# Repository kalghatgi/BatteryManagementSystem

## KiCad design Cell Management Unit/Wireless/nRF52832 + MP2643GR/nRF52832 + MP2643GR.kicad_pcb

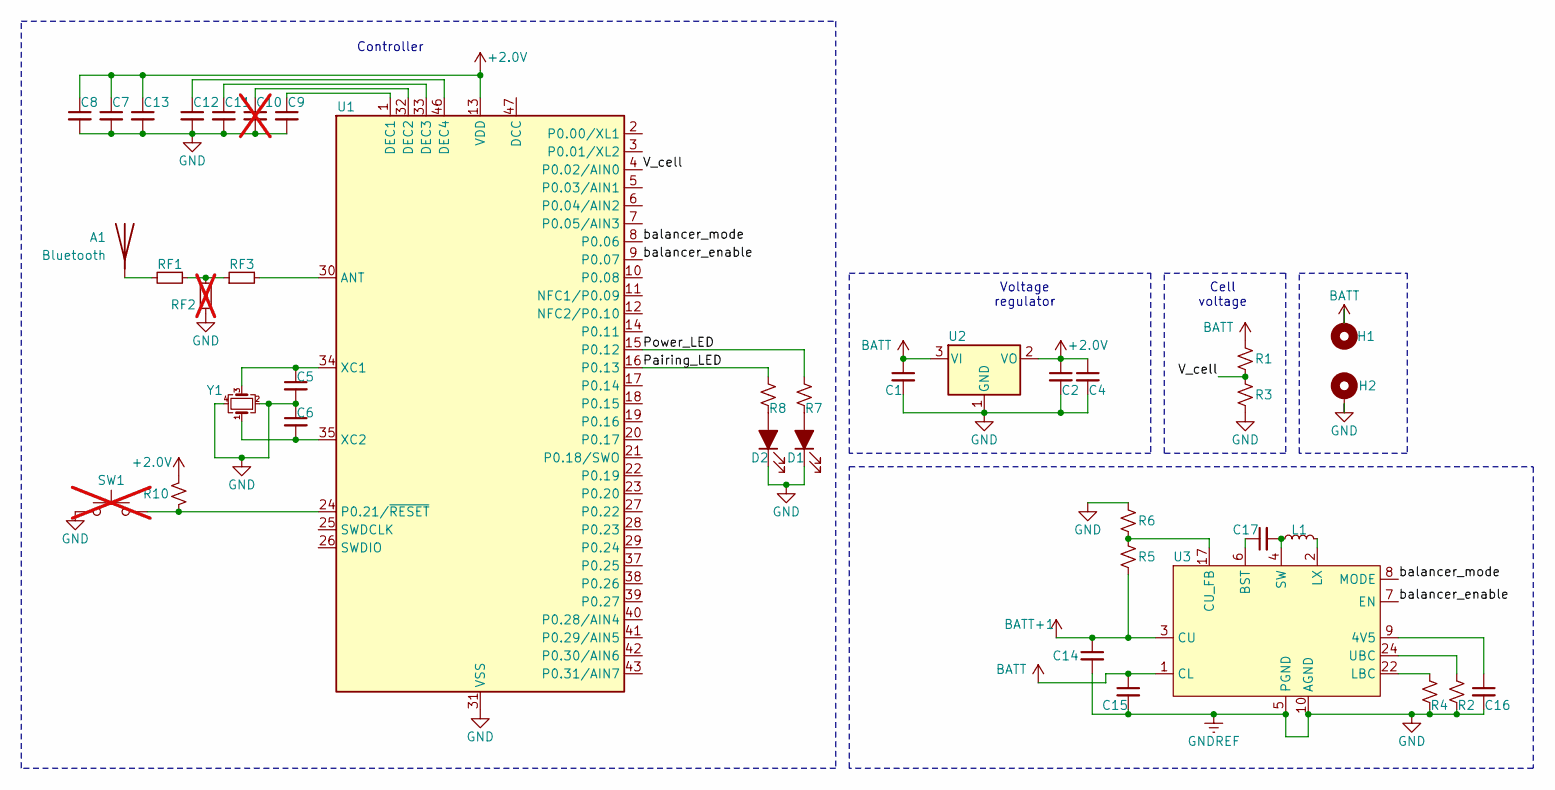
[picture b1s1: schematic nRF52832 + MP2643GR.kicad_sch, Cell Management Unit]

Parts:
A1: Bluetooth; L_1206_3216Metric; MPN RFANT3216120A5T
C1: 1uF, 10V; C_0402_1005Metric
C2, C4: 10uF, 4V; C_0402_1005Metric
C5, C6: 10pF, 4V; C_0402_1005Metric
C7, C9, C13: 100nF, 4V; C_0402_1005Metric
C8: 4.7uF, 4V; C_0402_1005Metric
C10: 100nF, 4V; C_0201_0603Metric; not fitted
C11: 100pF, 4V; C_0201_0603Metric
C12: 1uF, 4V; C_0402_1005Metric
C14: 22uF, >=10V, 0805; C_0805_2012Metric
C15: 22uF, >=6.3V, 0603; C_0603_1608Metric
C16: 1uF, >=10V, 0402; C_0402_1005Metric
C17: 22uF, >=10V, 0402; C_0402_1005Metric
D1: Red; LED_0402_1005Metric; MPN BL-HJE37A-AV-TRB
D2: Blue; LED_0402_1005Metric; MPN IN-S42BT5B
H1, H2: MountingHole_Pad; MountingHole_5.3mm_M5_Pad_Via
L1: 2.2uH, <50mOhm; L_Coilcraft_XxL4030; MPN ASPI-4030S-2R2N-T
R1: 15K, 62.5mW, <=1%, 0402; R_0402_1005Metric
R2: 107K, 62.5mW, 0402; R_0402_1005Metric
R3: 10K, 62.5mW, <= 1%, 0402; R_0402_1005Metric
R4: 133K, 62.5mW, <= 1%, 0402; R_0402_1005Metric
R5, R6: 10K, 62.5mW, <= 1%; R_0402_1005Metric
R7, R8: 4.7K, 62.5mW, 0402; R_0402_1005Metric
R10: 2.2K, 62.5mW; R_0402_1005Metric
RF1, RF3: C_0201_0603Metric
RF2: 0R, 62.5mW; C_0201_0603Metric; not fitted
SW1: SPST; SW_SPST_B3U-1000P; not fitted
U1: nRF52832-QFxx; QFN-48-1EP_6x6mm_P0.4mm_EP4.6x4.6mm
U2: 2.0V, >100mA; SOT-23; MPN MCP1700T-2002E-TT
U3: MP2643GR-Z; MP2643
Y1: 32MHz, 10ppm; US3200005Z_1612

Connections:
+2.0V: C2.1, C4.1, C7.1, C8.1, C13.1, R10.1, U1.13 (VDD), U1.36 (VDD), U1.48 (VDD), U2.2 (VO)
/Pairing_LED: R8.1, U1.16 (P0.13)
/Power_LED: R7.1, U1.15 (P0.12)
/V_cell: R1.2, R3.1, U1.4 (P0.02/AIN0)
/balancer_enable: U1.9 (P0.07), U3.7 (EN)
/balancer_mode: U1.8 (P0.06), U3.8 (MODE)
BATT: C1.1, C15.1, H1.1, R1.1, U2.3 (VI), U3.1 (CL)
BATT+1: C14.1, R5.2, U3.3 (CU)
GND: C1.2, C2.2, C4.2, C5.2, C6.1, C7.2, C8.2, C9.2, C10.2, C11.2, C12.2, C13.2, C14.2, C15.2, C16.2, D1.1 (K), D2.1 (K), H2.1, R2.2, R3.2, R4.2, R6.1, RF2.1, SW1.1, U1.31 (VSS), U1.45 (VSS), U1.49 (VSS), U2.1 (GND), U3.5 (PGND), U3.10 (AGND), U3.11 (AGND), U3.12 (AGND), U3.13 (AGND), U3.14 (AGND), U3.15 (AGND), U3.16 (AGND), U3.23 (AGND), U3.25 (AGND), U3.26 (AGND), Y1.2, Y1.4
LOGIC: C16.1, U3.9 (4V5), U3.18 (LOGIC)
unnamed: A1.1 (A), RF1.2
unnamed: D1.2 (A), R7.2
unnamed: D2.2 (A), R8.2
unnamed: RF1.1, RF2.2, RF3.1
unnamed: RF3.2, U1.30 (ANT)
unnamed: C9.1, U1.1 (DEC1)
unnamed: C10.1, U1.32 (DEC2)
unnamed: C11.1, U1.33 (DEC3)
unnamed: C12.1, U1.46 (DEC4)
unnamed: R10.2, SW1.2, U1.24 (P0.21/~RESET)
unnamed: C5.1, U1.34 (XC1), Y1.3
unnamed: C6.2, U1.35 (XC2), Y1.1
unnamed: C17.1, U3.6 (BST)
unnamed: R5.1, R6.2, U3.17 (CU_FB)
unnamed: R4.1, U3.22 (LBC)
unnamed: L1.2, U3.2 (LX)
unnamed: C17.2, L1.1, U3.4 (SW)
unnamed: R2.1, U3.24 (UBC)

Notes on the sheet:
Controller
Cell voltage
Voltage regulator

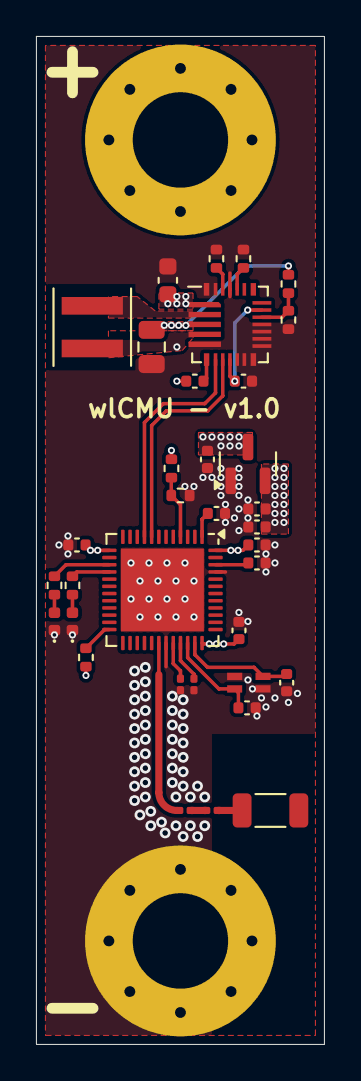
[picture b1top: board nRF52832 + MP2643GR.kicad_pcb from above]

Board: 4 copper layers, 16.0 x 56.0 mm, 37 parts (0 on the bottom side), 28 nets.

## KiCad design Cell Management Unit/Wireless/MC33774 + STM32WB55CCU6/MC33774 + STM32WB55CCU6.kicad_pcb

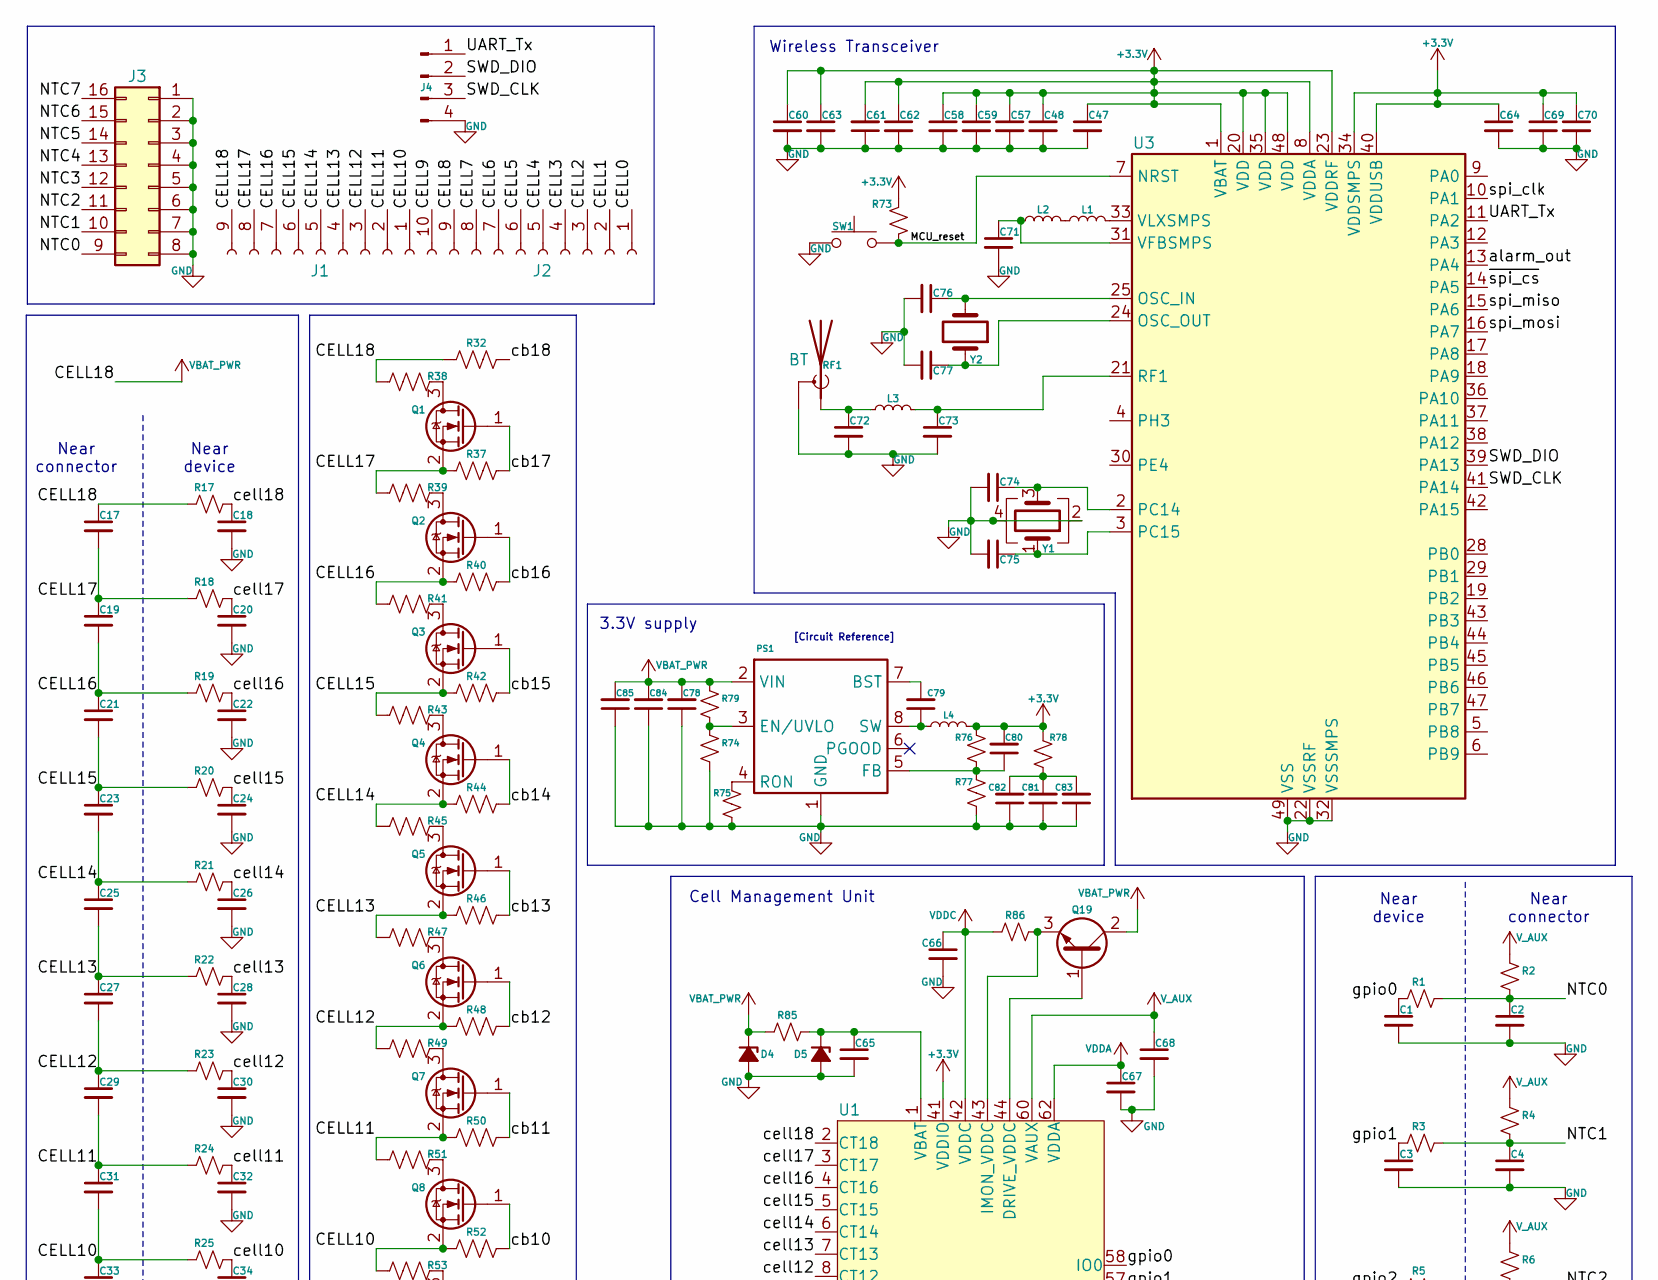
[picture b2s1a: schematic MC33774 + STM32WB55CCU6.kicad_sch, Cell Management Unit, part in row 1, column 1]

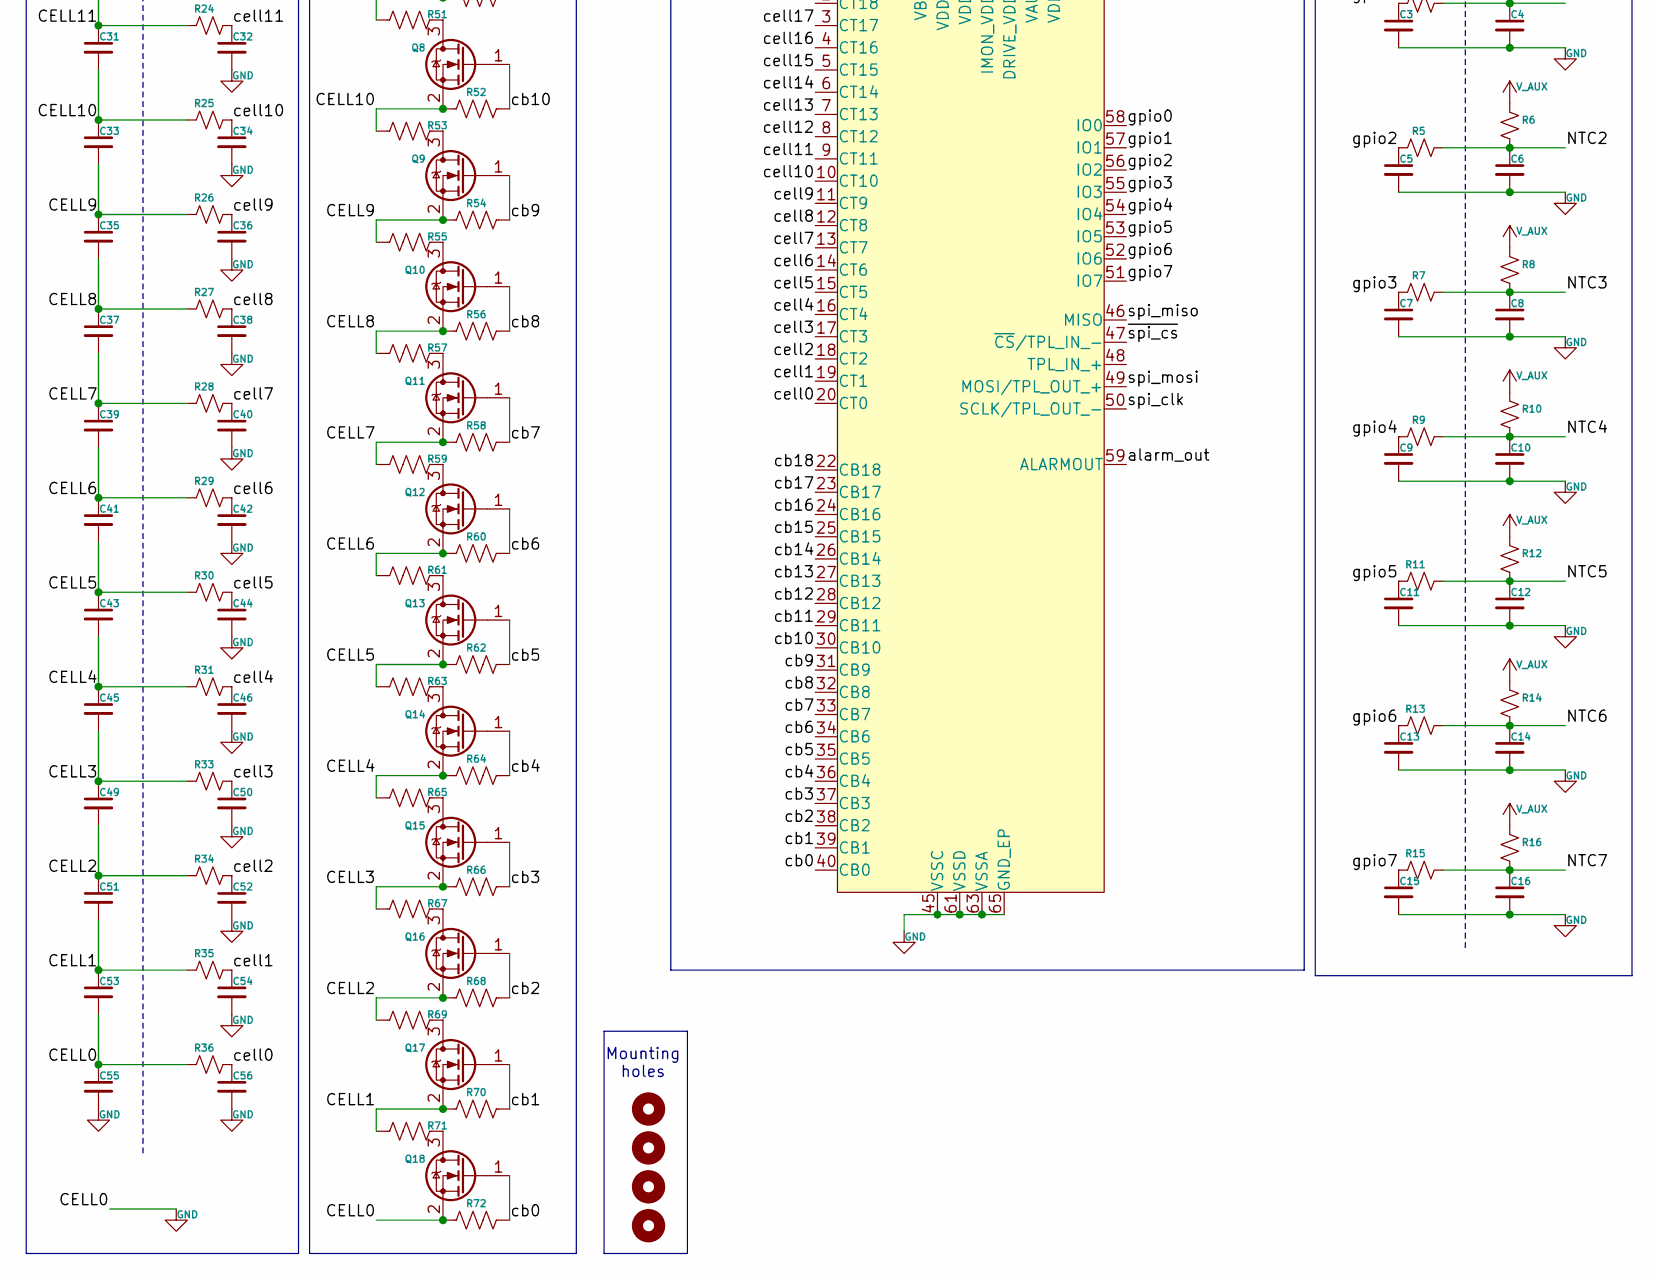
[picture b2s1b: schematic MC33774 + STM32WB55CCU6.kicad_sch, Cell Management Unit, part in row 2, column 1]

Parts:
C1, C2, C3, C4, C5, C6, C7, C8, C9, C10, C11, C12, C13, C14, C15, C16, C17, C19, C21, C23, C25, C27, C29, C31, C33, C35, C37, C39, C41, C43, C45, C49, C51, C53, C55: 47nF 10V 0402; C_0402_1005Metric
C18, C20, C22, C24, C26, C28, C30, C32, C34, C36, C38, C40, C42, C44, C46, C50, C52, C54, C56: 47nF 100V 0603; C_0603_1608Metric
C47, C48, C57, C59, C60, C62, C64, C70: 100nF 6.3V 0402; C_0402_1005Metric; MPN cc0402zpy5v7bb104
C58, C69, C71: 4.7uF 6.3V 0402; C_0402_1005Metric; MPN cl05a475mq5nrnc
C61: 1uF 6.3V 0402; C_0402_1005Metric; MPN cl05a105kq5nnnc
C63: 100pF 6.3V 0402; C_0402_1005Metric
C65: 100nF 100V 0805; C_0805_2012Metric
C66: 470nF 25V 0402; C_0402_1005Metric
C67, C68: 100nF 25V 0402; C_0402_1005Metric
C72: 1pF 6.3V 0402; C_0402_1005Metric
C73: 1.5pF 6.3V 0402; C_0402_1005Metric
C74, C75: 18pF 6.3V 0603; C_0603_1608Metric; MPN c0805c180m3hactu
C76, C77: 9pF 6.3V 0603; C_0603_1608Metric; MPN mc0603n9r0d500ct
C78, C84, C85: 1uF 100V 1206; C_1210_3225Metric
C79: 2.2nF 25V 0402; C_0402_1005Metric
C80: 100pF 25V 0805; C_0603_1608Metric
C81, C82, C83: 2.2uF 6.3V 0402; C_0805_2012Metric
D4: TVS, Vstandoff = 80V, Vbreakdown = 90V, SOD-123; D_SOD-123
D5: TVS, Vbreakdown = 84V, SOD-123; D_SOD-123
H1, H2, H3, H4: MountingHole; MountingHole_3.2mm_M3_ISO7380_Pad
J1: Conn_01x09_Socket; Molex_Micro-Fit_3.0_43650-0900_1x09_P3.00mm_Horizontal
J2: Conn_01x10_Socket; Molex_Micro-Fit_3.0_43650-1000_1x10_P3.00mm_Horizontal
J3: Conn_02x08_Counter_Clockwise; Molex_Micro-Fit_3.0_43045-1600_2x08_P3.00mm_Horizontal
J4: Conn_01x04_Pin; PinHeader_1x04_P2.54mm_Vertical_SMD_Pin1Left
L1: 10nH, 100mA, 0402; L_0402_1005Metric; MPN mcft000030
L2: 10uH, 100mA, 0805; L_0805_2012Metric; MPN mcl2012v1-100-r
L3: 2.2nH 0402; L_0402_1005Metric
L4: 68uH 30mOhm; L_Taiyo-Yuden_MD-4040; MPN aspi-0425-680m-t3
PS1: Vin=100V Iout=0.2A; SOIC-8-1EP_3.9x4.9mm_P1.27mm_EP2.29x3mm_ThermalVias; MPN LM5168F
Q1, Q2, Q3, Q4, Q5, Q6, Q7, Q8, Q9, Q10, Q11, Q12, Q13, Q14, Q15, Q16, Q17, Q18: 10V 5A SOT-23; SOT-23
Q19: NPN, 150V 2A; SOT-223-3_TabPin2
R1, R3, R5, R7, R9, R11, R13, R15: 5K 0.0625W 0402; R_0402_1005Metric
R2, R4, R6, R8, R10, R12, R14, R16, R17, R18, R19, R20, R21, R22, R23, R24, R25, R26, R27, R28, R29, R30, R31, R33, R34, R35, R36: 10K 0.0625W 0402; R_0402_1005Metric
R32, R37, R40, R42, R44, R46, R48, R50, R52, R54, R56, R58, R60, R62, R64, R66, R68, R70, R72: 47E 0.25W 0603; R_0603_1608Metric
R38, R39, R41, R43, R45, R47, R49, R51, R53, R55, R57, R59, R61, R63, R65, R67, R69, R71: 4E 5W; 35503R9JT - TE connectivity
R73: 10K 0.100W 0603; R_0603_1608Metric; MPN mr06x103-jtlv
R74: 34K 0.100W 0603; R_0603_1608Metric
R75: 27.4K 0.0625W 0402; R_0603_1608Metric
R76: 178K 0.100W 0402; R_0402_1005Metric
R77: 101K 0.100W 0402; R_0402_1005Metric
R78: 0.180R 0.100W 0603; R_0603_1608Metric
R79: 100K 0.125W 0805; R_0805_2012Metric; MPN mcwr08x1003ftl
R85: 10E 0.100W 0603; R_0603_1608Metric
R86: 180E 0.0625W 0402; R_0402_1005Metric
RF1: Texas_SWRA117D_2.4GHz_Right
SW1: 2-pin tactile switch SPST; SW_Push_SPST_NO_Alps_SKRK; MPN TS342
U1: 18 cells; LQFP-64-1EP_10x10mm_P0.5mm_EP6.5x6.5mm_ThermalVias
U3: STM32WB55CCU6; QFN-48-1EP_7x7mm_P0.5mm_EP5.15x5.15mm_ThermalVias
Y1: 32MHz 3225; Crystal_SMD_Abracon_ABM8AIG-4Pin_3.2x2.5mm
Y2: 32.768KHz 3215; Crystal_SMD_3215-2Pin_3.2x1.5mm; MPN mpjk-7l-32-768-12-5-20-70-c

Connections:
+3.3V: C47.1, C48.1, C57.1, C58.1, C59.1, C60.1, C61.2, C62.1, C63.1, C64.1, C69.1, C70.1, C80.2, L4.2, R73.1, R76.1, R78.1, U1.41 (VDDIO), U3.1 (VBAT), U3.8 (VDDA), U3.20 (VDD), U3.23 (VDDRF), U3.34 (VDDSMPS), U3.35 (VDD), U3.40 (VDDUSB), U3.48 (VDD)
/CELL1: C51.2, C53.1, J2.2, Q17.2 (S), R35.1, R70.1, R71.1
/CELL2: C49.2, C51.1, J2.3, Q16.2 (S), R34.1, R68.1, R69.1
/CELL3: C45.2, C49.1, J2.4, Q15.2 (S), R33.1, R66.1, R67.1
/CELL4: C43.2, C45.1, J2.5, Q14.2 (S), R31.1, R64.1, R65.1
/CELL5: C41.2, C43.1, J2.6, Q13.2 (S), R30.1, R62.1, R63.1
/CELL6: C39.2, C41.1, J2.7, Q12.2 (S), R29.1, R60.1, R61.1
/CELL7: C37.2, C39.1, J2.8, Q11.2 (S), R28.1, R58.1, R59.1
/CELL8: C35.2, C37.1, J2.9, Q10.2 (S), R27.1, R56.1, R57.1
/CELL9: C33.2, C35.1, J2.10, Q9.2 (S), R26.1, R54.1, R55.1
/CELL10: C31.2, C33.1, J1.1, Q8.2 (S), R25.1, R52.1, R53.1
/CELL11: C29.2, C31.1, J1.2, Q7.2 (S), R24.1, R50.1, R51.1
/CELL12: C27.2, C29.1, J1.3, Q6.2 (S), R23.1, R48.1, R49.1
/CELL13: C25.2, C27.1, J1.4, Q5.2 (S), R22.1, R46.1, R47.1
/CELL14: C23.2, C25.1, J1.5, Q4.2 (S), R21.1, R44.1, R45.1
/CELL15: C21.2, C23.1, J1.6, Q3.2 (S), R20.1, R42.1, R43.1
/CELL16: C19.2, C21.1, J1.7, Q2.2 (S), R19.1, R40.1, R41.1
/CELL17: C17.2, C19.1, J1.8, Q1.2 (S), R18.1, R37.1, R39.1
/MCU_reset: R73.2, SW1.1, U3.7 (NRST)
/NTC0: C2.1, J3.9, R1.2, R2.2
/NTC1: C4.1, J3.10, R3.2, R4.2
/NTC2: C6.1, J3.11, R5.2, R6.2
/NTC3: C8.1, J3.12, R7.2, R8.2
/NTC4: C10.1, J3.13, R9.2, R10.2
/NTC5: C12.1, J3.14, R11.2, R12.2
/NTC6: C14.1, J3.15, R13.2, R14.2
/NTC7: C16.1, J3.16, R15.2, R16.2
/SWD_CLK: J4.3, U3.41 (PA14)
/SWD_DIO: J4.2, U3.39 (PA13)
/UART_Tx: J4.1, U3.11 (PA2)
/alarm_out: U1.59 (ALARMOUT), U3.13 (PA4)
/cb0: Q18.1 (G), R72.2, U1.40 (CB0)
/cb1: Q17.1 (G), R70.2, U1.39 (CB1)
/cb2: Q16.1 (G), R68.2, U1.38 (CB2)
/cb3: Q15.1 (G), R66.2, U1.37 (CB3)
/cb4: Q14.1 (G), R64.2, U1.36 (CB4)
/cb5: Q13.1 (G), R62.2, U1.35 (CB5)
/cb6: Q12.1 (G), R60.2, U1.34 (CB6)
/cb7: Q11.1 (G), R58.2, U1.33 (CB7)
/cb8: Q10.1 (G), R56.2, U1.32 (CB8)
/cb9: Q9.1 (G), R54.2, U1.31 (CB9)
/cb10: Q8.1 (G), R52.2, U1.30 (CB10)
/cb11: Q7.1 (G), R50.2, U1.29 (CB11)
/cb12: Q6.1 (G), R48.2, U1.28 (CB12)
/cb13: Q5.1 (G), R46.2, U1.27 (CB13)
/cb14: Q4.1 (G), R44.2, U1.26 (CB14)
/cb15: Q3.1 (G), R42.2, U1.25 (CB15)
/cb16: Q2.1 (G), R40.2, U1.24 (CB16)
/cb17: Q1.1 (G), R37.2, U1.23 (CB17)
/cb18: R32.2, U1.22 (CB18)
/cell0: C56.1, R36.2, U1.20 (CT0)
/cell1: C54.1, R35.2, U1.19 (CT1)
/cell2: C52.1, R34.2, U1.18 (CT2)
/cell3: C50.1, R33.2, U1.17 (CT3)
/cell4: C46.1, R31.2, U1.16 (CT4)
/cell5: C44.1, R30.2, U1.15 (CT5)
/cell6: C42.1, R29.2, U1.14 (CT6)
/cell7: C40.1, R28.2, U1.13 (CT7)
/cell8: C38.1, R27.2, U1.12 (CT8)
/cell9: C36.1, R26.2, U1.11 (CT9)
/cell10: C34.1, R25.2, U1.10 (CT10)
/cell11: C32.1, R24.2, U1.9 (CT11)
/cell12: C30.1, R23.2, U1.8 (CT12)
/cell13: C28.1, R22.2, U1.7 (CT13)
/cell14: C26.1, R21.2, U1.6 (CT14)
/cell15: C24.1, R20.2, U1.5 (CT15)
/cell16: C22.1, R19.2, U1.4 (CT16)
/cell17: C20.1, R18.2, U1.3 (CT17)
/cell18: C18.1, R17.2, U1.2 (CT18)
/gpio0: C1.1, R1.1, U1.58 (IO0)
/gpio1: C3.1, R3.1, U1.57 (IO1)
/gpio2: C5.1, R5.1, U1.56 (IO2)
/gpio3: C7.1, R7.1, U1.55 (IO3)
/gpio4: C9.1, R9.1, U1.54 (IO4)
/gpio5: C11.1, R11.1, U1.53 (IO5)
/gpio6: C13.1, R13.1, U1.52 (IO6)
/gpio7: C15.1, R15.1, U1.51 (IO7)
/spi_clk: U1.50 (SCLK/TPL_OUT_-), U3.10 (PA1)
/spi_miso: U1.46 (MISO), U3.15 (PA6)
/spi_mosi: U1.49 (MOSI/TPL_OUT_+), U3.16 (PA7)
/~spi_cs: U1.47 (~CS/TPL_IN_-), U3.14 (PA5)
GND: C1.2, C2.2, C3.2, C4.2, C5.2, C6.2, C7.2, C8.2, C9.2, C10.2, C11.2, C12.2, C13.2, C14.2, C15.2, C16.2, C18.2, C20.2, C22.2, C24.2, C26.2, C28.2, C30.2, C32.2, C34.2, C36.2, C38.2, C40.2, C42.2, C44.2, C46.2, C47.2, C48.2, C50.2, C52.2, C53.2, C54.2, C55.1, C55.2, C56.2, C57.2, C58.2, C59.2, C60.2, C61.1, C62.2, C63.2, C64.2, C65.2, C66.2, C67.2, C68.2, C69.2, C70.2, C71.2, C72.2, C73.2, C74.2, C75.2, C76.2, C77.2, C78.1, C81.1, C82.1, C83.1, C84.1, C85.1, D4.2 (A), D5.2 (A), J2.1, J3.1, J3.2, J3.3, J3.4, J3.5, J3.6, J3.7, J3.8, J4.4, PS1.1 (GND), PS1.9 (GND_thermal), Q18.2 (S), R36.1, R72.1, R74.2, R75.1, R77.2, RF1.2 (Shield), SW1.2, U1.45 (VSSC), U1.61 (VSSD), U1.63 (VSSA), U1.65 (GND_EP), U3.22 (VSSRF), U3.32 (VSSSMPS), U3.49 (VSS), Y1.2, Y1.4
unnamed: C81.2, C82.2, C83.2, R78.2
unnamed: C65.1, D5.1 (K), R85.1, U1.1 (VBAT)
unnamed: L1.1, L2.2
unnamed: C79.2, PS1.7 (BST)
unnamed: PS1.3 (EN/UVLO), R74.1, R79.2
unnamed: C80.1, PS1.5 (FB), R76.2, R77.1
unnamed: PS1.4 (RON), R75.2
unnamed: C79.1, L4.1, PS1.8 (SW)
unnamed: Q1.3 (D), R38.2
unnamed: Q2.3 (D), R39.2
unnamed: Q3.3 (D), R41.2
unnamed: Q4.3 (D), R43.2
unnamed: Q5.3 (D), R45.2
unnamed: Q6.3 (D), R47.2
unnamed: Q7.3 (D), R49.2
unnamed: Q8.3 (D), R51.2
unnamed: Q9.3 (D), R53.2
unnamed: Q10.3 (D), R55.2
unnamed: Q11.3 (D), R57.2
unnamed: Q12.3 (D), R59.2
unnamed: Q13.3 (D), R61.2
unnamed: Q14.3 (D), R63.2
unnamed: Q15.3 (D), R65.2
unnamed: Q16.3 (D), R67.2
unnamed: Q17.3 (D), R69.2
unnamed: Q18.3 (D), R71.2
unnamed: Q19.1 (B), U1.44 (DRIVE_VDDC)
unnamed: Q19.3 (E), R86.1, U1.43 (IMON_VDDC)
unnamed: C72.1, L3.1, RF1.1 (A)
unnamed: C76.1, U3.25 (OSC_IN), Y2.2
unnamed: C77.1, U3.24 (OSC_OUT), Y2.1
unnamed: C74.1, U3.2 (PC14), Y1.3
unnamed: C75.1, U3.3 (PC15), Y1.1
unnamed: C73.1, L3.2, U3.21 (RF1)
unnamed: C71.1, L2.1, U3.31 (VFBSMPS)
unnamed: L1.2, U3.33 (VLXSMPS)
VBAT_PWR: C17.1, C78.2, C84.2, C85.2, D4.1 (K), J1.9, PS1.2 (VIN), Q19.2 (C), R17.1, R32.1, R38.1, R79.1, R85.2
VDDA: C67.1, U1.62 (VDDA)
VDDC: C66.1, R86.2, U1.42 (VDDC)
V_AUX: C68.1, R2.1, R4.1, R6.1, R8.1, R10.1, R12.1, R14.1, R16.1, U1.60 (VAUX)

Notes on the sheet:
Cell Management Unit
3.3V supply
Mounting holes
[Circuit Reference]
Near connector
Near device
Wireless Transceiver

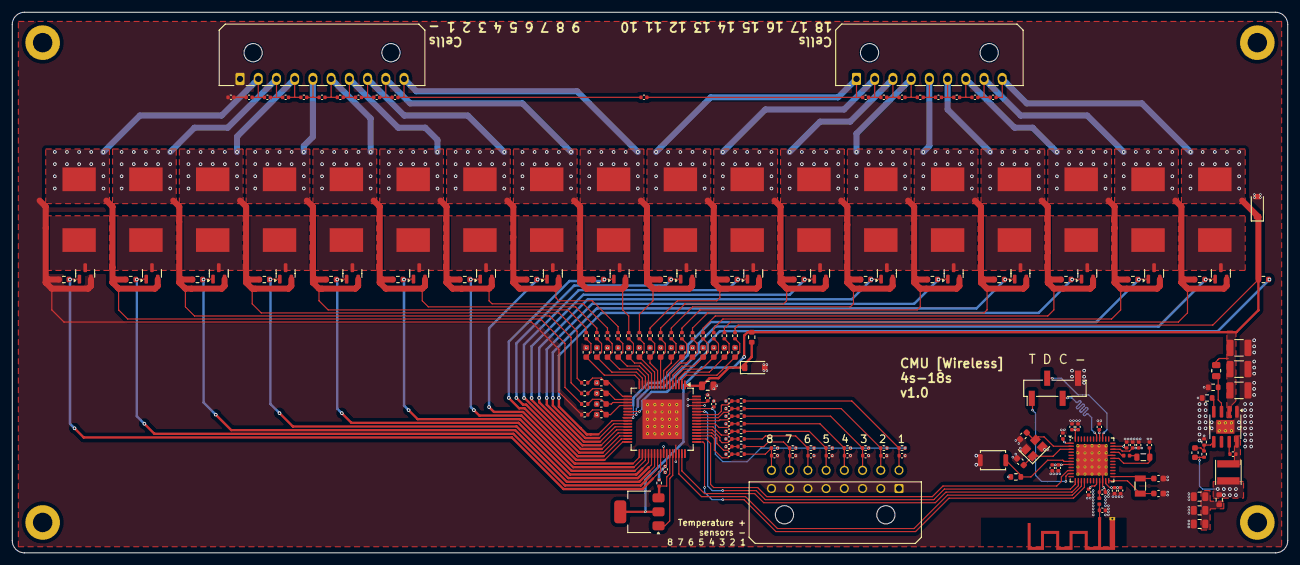
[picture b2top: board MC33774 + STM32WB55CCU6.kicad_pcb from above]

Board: 4 copper layers, 210.0 x 89.0 mm, 206 parts (0 on the bottom side), 122 nets.

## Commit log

2024-07-25 Cell Management Unit/Wired/MC33774 - v1.0
2024-07-25 Cell Management Unit/Wireless/MC33774+STM32WB55CCU6 - v1.0
2025-05-25 Cell Management Unit/Wireless/nRF52832 - v1.0
2025-06-19 Cell ManagementSystem\Wireless\nRF52832 + MP2643 - v1.0
